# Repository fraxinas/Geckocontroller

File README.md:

# Geckocontroller

(CC) 2021-2022 by Andreas Frisch <github@fraxinas.dev>

## OwO what's this?
**`geckocontroller` is an ESP32-based all-in-one solution for terrarium automation.**

|  |  |
| :------------------------------------------ | :----------------------------------------- |

## Hardware Features
### Relay Output
* 3 solid state relays with zero-cross switching
* individual load 1A each
* for HeatBed (/Fogger), HeatLamp and Pump

### Dimmer Output
* opto-coupler zero cross detection
* random cross solid state relay
* phase controller modulator

### RGB LED Output
* PWM driver
* for 12V RGB LED stripes

### FAN Output
* for an ATX type PC fan
* PWM and tachometer pins
* power cut-off circuitry for completely stopping all types of fans

### Dallas Thermometer Input
* 2 inputs for DS18B20 bus temperature sensors

### I²C Ports
* BME280 Thermo/Hygro/Baro sensor module (ceiling)
* SHT-3xD Thermo/Hygro sensor (ground)

### Load Cell Input
* HX711-based load cell amplifier/ADC
* for weighing / occupancy detection

### USB-C Port
* USB-to-serial programming port

### WiFi
* ESP32 wifi client

### SPI / Addon Connector
* for future extensions like a display or console

### Documentation
* [Circuit Calculations](hardware/calculations/README.md)

## Software

### Using ESPHome.io
* simple YAML configuration for different sensor / actor modules
* Through Home Assistant web interface:
  * data logging and visualization of all environmental readings
  * manually control all actors, modify set points of controllers

### Weather Simulation
* use Nouvelle-Calédonie (Crested Gecko's natural habitat) real weather records
* use temperature, humidity, rain and sky cover values for creating a realistic varied simulation of the habitants' indigenous environment
* simulated sunrise, sunset, lightening storm

### Documentation
* [How-to Setup & Calibrate](software/README.md)

## Console unit
|     |     |
| :------------------------------------------ | :----------------------------------------- |
* Stand-alone device based on ESP32
* remote controls the main unit through home assistant via WiFi
* 240x240 IPS Display
* Rotary encoder + navigation button
* MH-Z19 CO<sub>2</sub> Sensor
* 6x WS2812 addressable RGB LEDs
* Piezo Buzzer for audio alerts
* USB-C powered
* custom esphome components:
  * controls for thermostat, hygrostat, rain, fogger
  * HSV color picker for scenic light

## TODO
### Console unit
- [X] schematic & PCB layout
- [ ] 3d case
- [X] CO2 sensor
- [X] WS2812 RGB LEDs
- [X] buzzer
- [X] software for ST7789 display
- [X] software for rotary encoder
- [ ] VCNL4040 support
- [ ] photos / documentation

### Controller unit
- [x] 3d-printed cases for BME280 sensor and console
- [x] rainfall/humidity automation
- [x] ventilation automation
- [x] moonlight simulation
- [x] thunderstorm simulation
- [ ] photos / documentation

## Project Diary
| Date       | Version | Milestone                                        |
| :--------- | :------ | :----------------------------------------------- |
| 2021-02-21 | v1.0    | Commission of 1st prototype PCB with aisler.net  |
| 2021-03-12 | v1.1    | First time programming of bodged prototype PCB   |
| 2021-04-10 |         | Fixed hardware issues with [LeoDJ](https://github.com/LeoDJ) & [Patagona](https://github.com/patagonaa) |
| 2021-04-15 | v1.2    | Commission of 2nd revision PCB with aisler.net   |
| 2021-05-03 | v1.2    | Completed PCB assembly, all modules working      |
| 2021-05-16 | v1.2    | Assembling of case and first deployment of unit  |
| 2022-01-02 |         | Added fogger to terrarium                        |
| 2022-01-09 |         | Base weather simulation on real historic records |
| 2022-01-28 | v1.0    | Order Console PCB at aisler.net & parts at LCSC  |
| 2022-02-18 |         | Assembled Console PCB                            |
| 2022-03-07 | v2.0    | New Hardware Revision of Console PCB             |

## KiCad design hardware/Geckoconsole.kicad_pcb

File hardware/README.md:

# Geckocontroller Hardware

## Calculations

### ACT4088 Feedback Resistors

with
* V<sub>out</sub> = 3.3V
* R<sub>FB1</sub> chosen 47k

* R<sub>FB2</sub> = R<sub>FB1</sub> / ((V<sub>out</sub> / 0.81) - 1) = 15289.156626506

Values are:
* `R103` = 47k
* `R101` = 15k
* `R102` = 287R

### HX711 Reference Voltage Resistors

with
* AVDD should be 100mV below VCC, so 3.20V
* AVDD = V<sub>BG</sub> * ( R1 + R2 ) / R2
* R1 chosen 47k

Values are:
* `R61` = 47k
* `R62` = 30k1

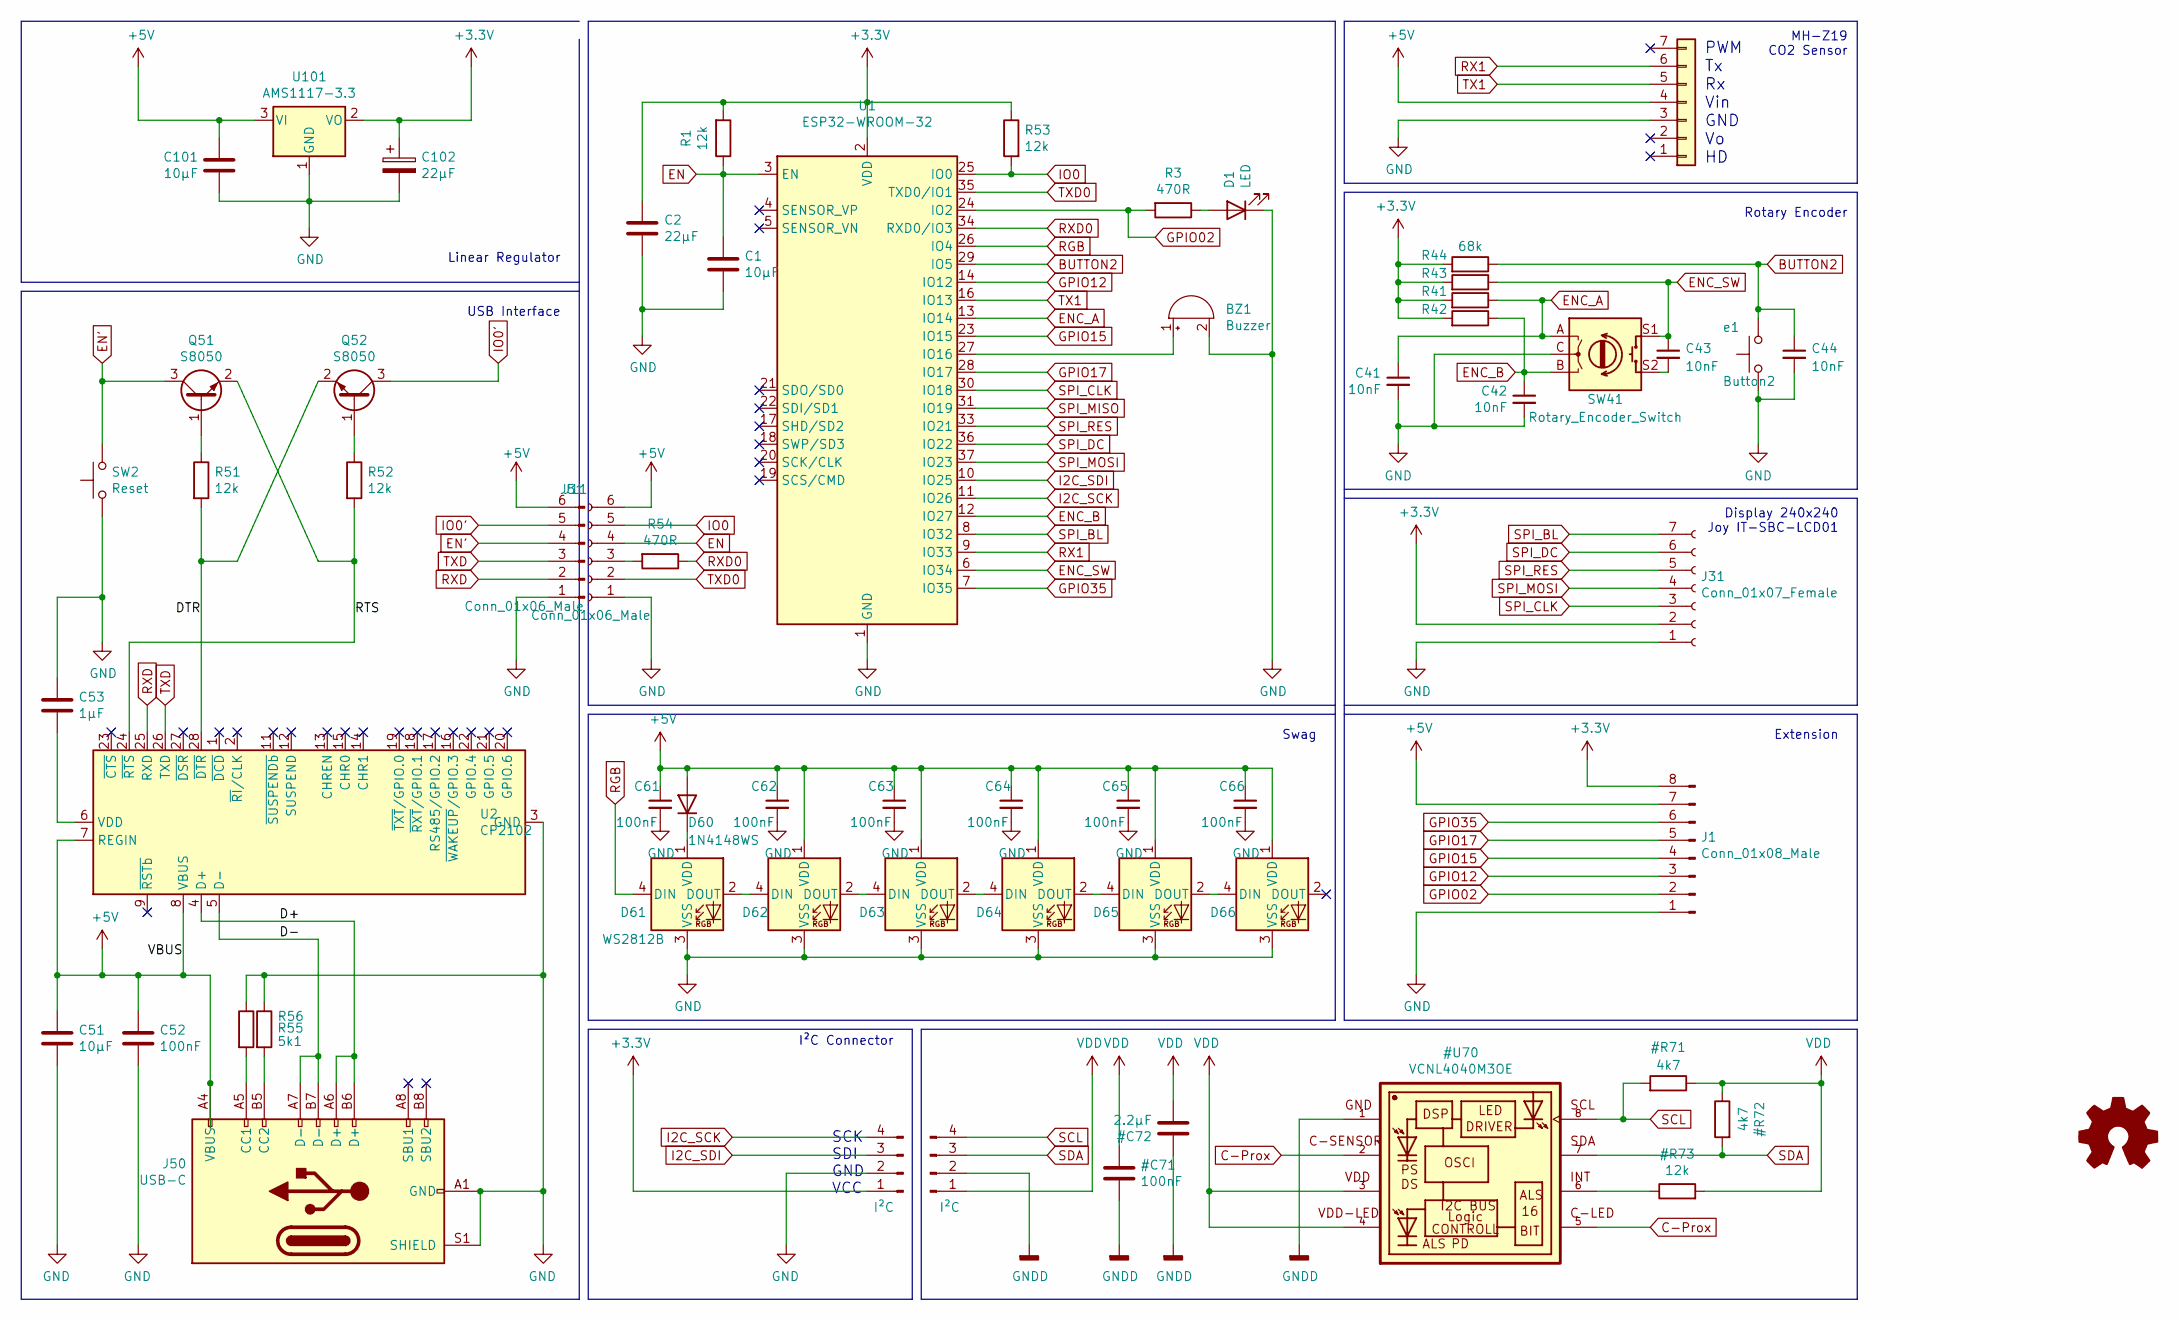
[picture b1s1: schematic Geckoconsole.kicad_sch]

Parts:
BZ1: Buzzer; Buzzer_Murata_PKMCS0909E4000-R1
C1, C51, C101: 10µF; C_0805_2012Metric_Pad1.18x1.45mm_HandSolder
C2: 22µF; C_1210_3225Metric_Pad1.33x2.70mm_HandSolder
C41, C42, C43, C44: 10nF; C_0603_1608Metric_Pad1.08x0.95mm_HandSolder
C52, C61, C62, C63, C64, C65, C66: 100nF; C_0603_1608Metric_Pad1.08x0.95mm_HandSolder
C53: 1µF; C_0603_1608Metric_Pad1.08x0.95mm_HandSolder
C102: 22µF; CP_Elec_4x5.3
D1: LED; LED_0805_2012Metric_Pad1.15x1.40mm_HandSolder
D60: 1N4148WS; D_SOD-323_HandSoldering
D61, D62, D63, D64, D65, D66: WS2812B; LED_WS2812B_PLCC4_5.0x5.0mm_P3.2mm
J1: Conn_01x08_Male; PinHeader_2x04_P2.54mm_Vertical
J11: Conn_01x06_Male; PinSocket_1x06_P2.00mm_Horizontal
J31: Conn_01x07_Female; PinSocket_1x07_P2.54mm_Vertical
J50: USB-C; USB_C_Receptacle_XKB_U262-16XN-4BVC11
J51: Conn_01x06_Male; PinHeader_1x06_P2.00mm_Horizontal
J70: I²C; PinSocket_1x04_P2.54mm_Vertical
J81: Conn_01x07; JST_PH_B7B-PH-K_1x07_P2.00mm_Vertical
LOGO1: Logo_Open_Hardware_Small; OSHW-Logo_5.7x6mm_Mask
Q51, Q52: S8050; SOT-23
R1, R51, R52, R53: 12k; R_0805_2012Metric_Pad1.20x1.40mm_HandSolder
R3, R54: 470R; R_0805_2012Metric_Pad1.20x1.40mm_HandSolder
R41, R42, R43, R44: 68k; R_0805_2012Metric_Pad1.20x1.40mm_HandSolder
R55, R56: 5k1; R_0805_2012Metric_Pad1.20x1.40mm_HandSolder
SW2: Reset; SW_SPST_B3U-1000P-B
SW41: Rotary_Encoder_Switch; Rotary_Encoder_Switched_PEC11R
U1: ESP32-WROOM-32
U2: CP2102; CP2102-QFN-28-modified
U101: AMS1117-3.3; SOT-223-3_TabPin2
e1: Button2; SW_PUSH_6mm_H5mm

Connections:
+3V3: C2.1, C102.1, J1.8, J31.2, J70.1, R1.2, R41.2, R42.2, R43.2, R44.2, R53.1, U1.2 (VDD), U101.2 (VO)
+5V: C51.1, C52.1, C61.1, C62.1, C63.1, C64.1, C65.1, C66.1, C101.1, D60.2 (A), D62.1 (VDD), D63.1 (VDD), D64.1 (VDD), D65.1 (VDD), D66.1 (VDD), J1.7, J11.6, J50.A4 (VBUS), J50.A9 (VBUS), J50.B4 (VBUS), J50.B9 (VBUS), J51.6, J81.4, U2.7 (REGIN), U2.8 (VBUS), U101.3 (VI)
/D+: J50.A6 (D+), J50.B6 (D+), U2.4 (D+)
/D-: J50.A7 (D-), J50.B7 (D-), U2.5 (D-)
/DTR: Q52.2 (E), R51.2, U2.28 (~DTR)
/RTS: Q51.2 (E), R52.2, U2.24 (~RTS)
BUTTON2: C44.1, R44.1, U1.29 (IO5), e1.2
EN: C1.1, J11.4, R1.1, U1.3 (EN)
EN': J51.4, Q51.3 (C), SW2.2
ENC_A: C41.1, R41.1, SW41.A, U1.13 (IO14)
ENC_B: C42.1, R42.1, SW41.B, U1.12 (IO27)
ENC_SW: C43.1, R43.1, SW41.S1, U1.6 (IO34)
GND: BZ1.2 (+), C1.2, C2.2, C41.2, C42.2, C44.2, C51.2, C52.2, C53.1, C61.2, C62.2, C63.2, C64.2, C65.2, C66.2, C101.2, C102.2, D1.1 (K), D61.3 (VSS), D62.3 (VSS), D63.3 (VSS), D64.3 (VSS), D65.3 (VSS), D66.3 (VSS), J1.1, J11.1, J31.1, J50.A1 (GND), J50.A12 (GND), J50.B1 (GND), J50.B12 (GND), J50.S1 (SHIELD), J51.1, J70.2, J81.3, R55.1, R56.1, SW2.1, SW41.C, U1.1 (GND), U1.15 (GND), U1.38 (GND), U1.39 (GND), U2.3 (GND), U2.29 (GND), U101.1 (GND), e1.1
GPIO02: J1.2, R3.2, U1.24 (IO2)
GPIO12: J1.3, U1.14 (IO12)
GPIO15: J1.4, U1.23 (IO15)
GPIO17: J1.5, U1.28 (IO17)
GPIO35: J1.6, U1.7 (IO35)
I2C_SCK: J70.4, U1.11 (IO26)
I2C_SDI: J70.3, U1.10 (IO25)
IO0: J11.5, R53.2, U1.25 (IO0)
IO0': J51.5, Q52.3 (C)
unnamed: BZ1.1 (-), U1.27 (IO16)
unnamed: C43.2, SW41.S2
unnamed: C53.2, U2.6 (VDD)
unnamed: D1.2 (A), R3.1
unnamed: D60.1 (K), D61.1 (VDD)
unnamed: D61.2 (DOUT), D62.4 (DIN)
unnamed: D62.2 (DOUT), D63.4 (DIN)
unnamed: D63.2 (DOUT), D64.4 (DIN)
unnamed: D64.2 (DOUT), D65.4 (DIN)
unnamed: D65.2 (DOUT), D66.4 (DIN)
unnamed: J11.3, R54.2
unnamed: J50.A5 (CC1), R56.2
unnamed: J50.B5 (CC2), R55.2
unnamed: Q51.1 (B), R51.1
unnamed: Q52.1 (B), R52.1
RGB: D61.4 (DIN), U1.26 (IO4)
RX1: J81.6, U1.9 (IO33)
RXD: J51.2, U2.25 (RXD)
RXD0: R54.1, U1.34 (RXD0/IO3)
SPI_BL: J31.7, U1.8 (IO32)
SPI_CLK: J31.3, U1.30 (IO18)
SPI_DC: J31.6, U1.36 (IO22)
SPI_MISO: U1.31 (IO19)
SPI_MOSI: J31.4, U1.37 (IO23)
SPI_RES: J31.5, U1.33 (IO21)
TX1: J81.5, U1.16 (IO13)
TXD: J51.3, U2.26 (TXD)
TXD0: J11.2, U1.35 (TXD0/IO1)

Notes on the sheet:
Display 240x240 Joy IT-SBC-LCD01
USB Interface
SCK SDI GND VCC
Linear Regulator
PWM Tx Rx Vin GND Vo HD
Rotary Encoder
I²C Connector
Swag
MH-Z19 CO2 Sensor
Extension

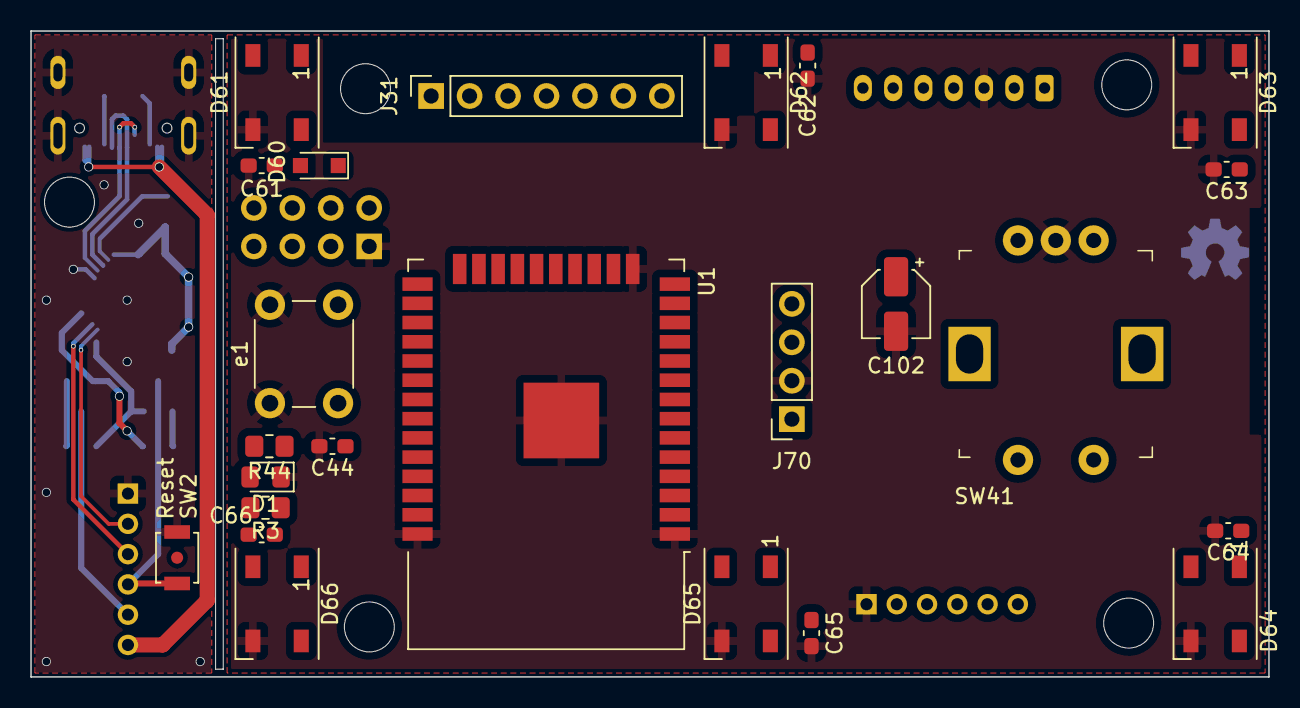
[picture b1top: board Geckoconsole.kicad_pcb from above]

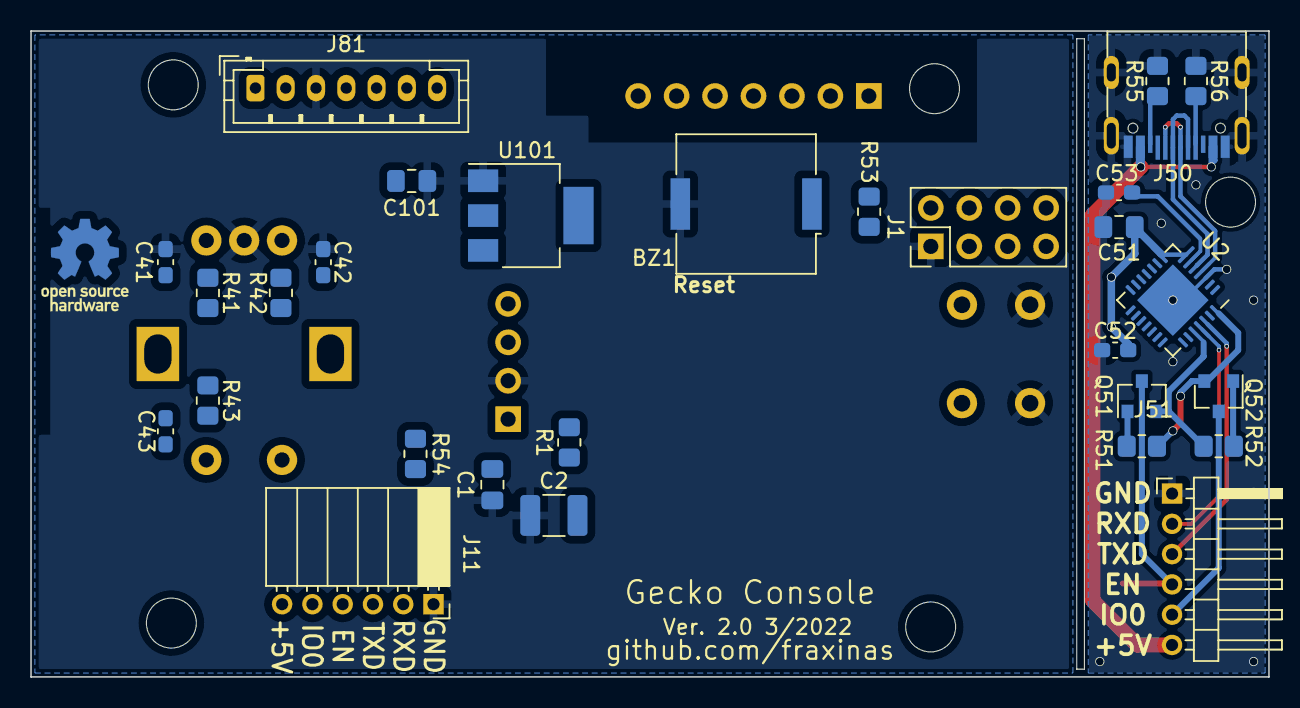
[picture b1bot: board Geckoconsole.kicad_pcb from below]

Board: 2 copper layers, 81.8 x 42.7 mm, 54 parts (30 on the bottom side), 49 nets.

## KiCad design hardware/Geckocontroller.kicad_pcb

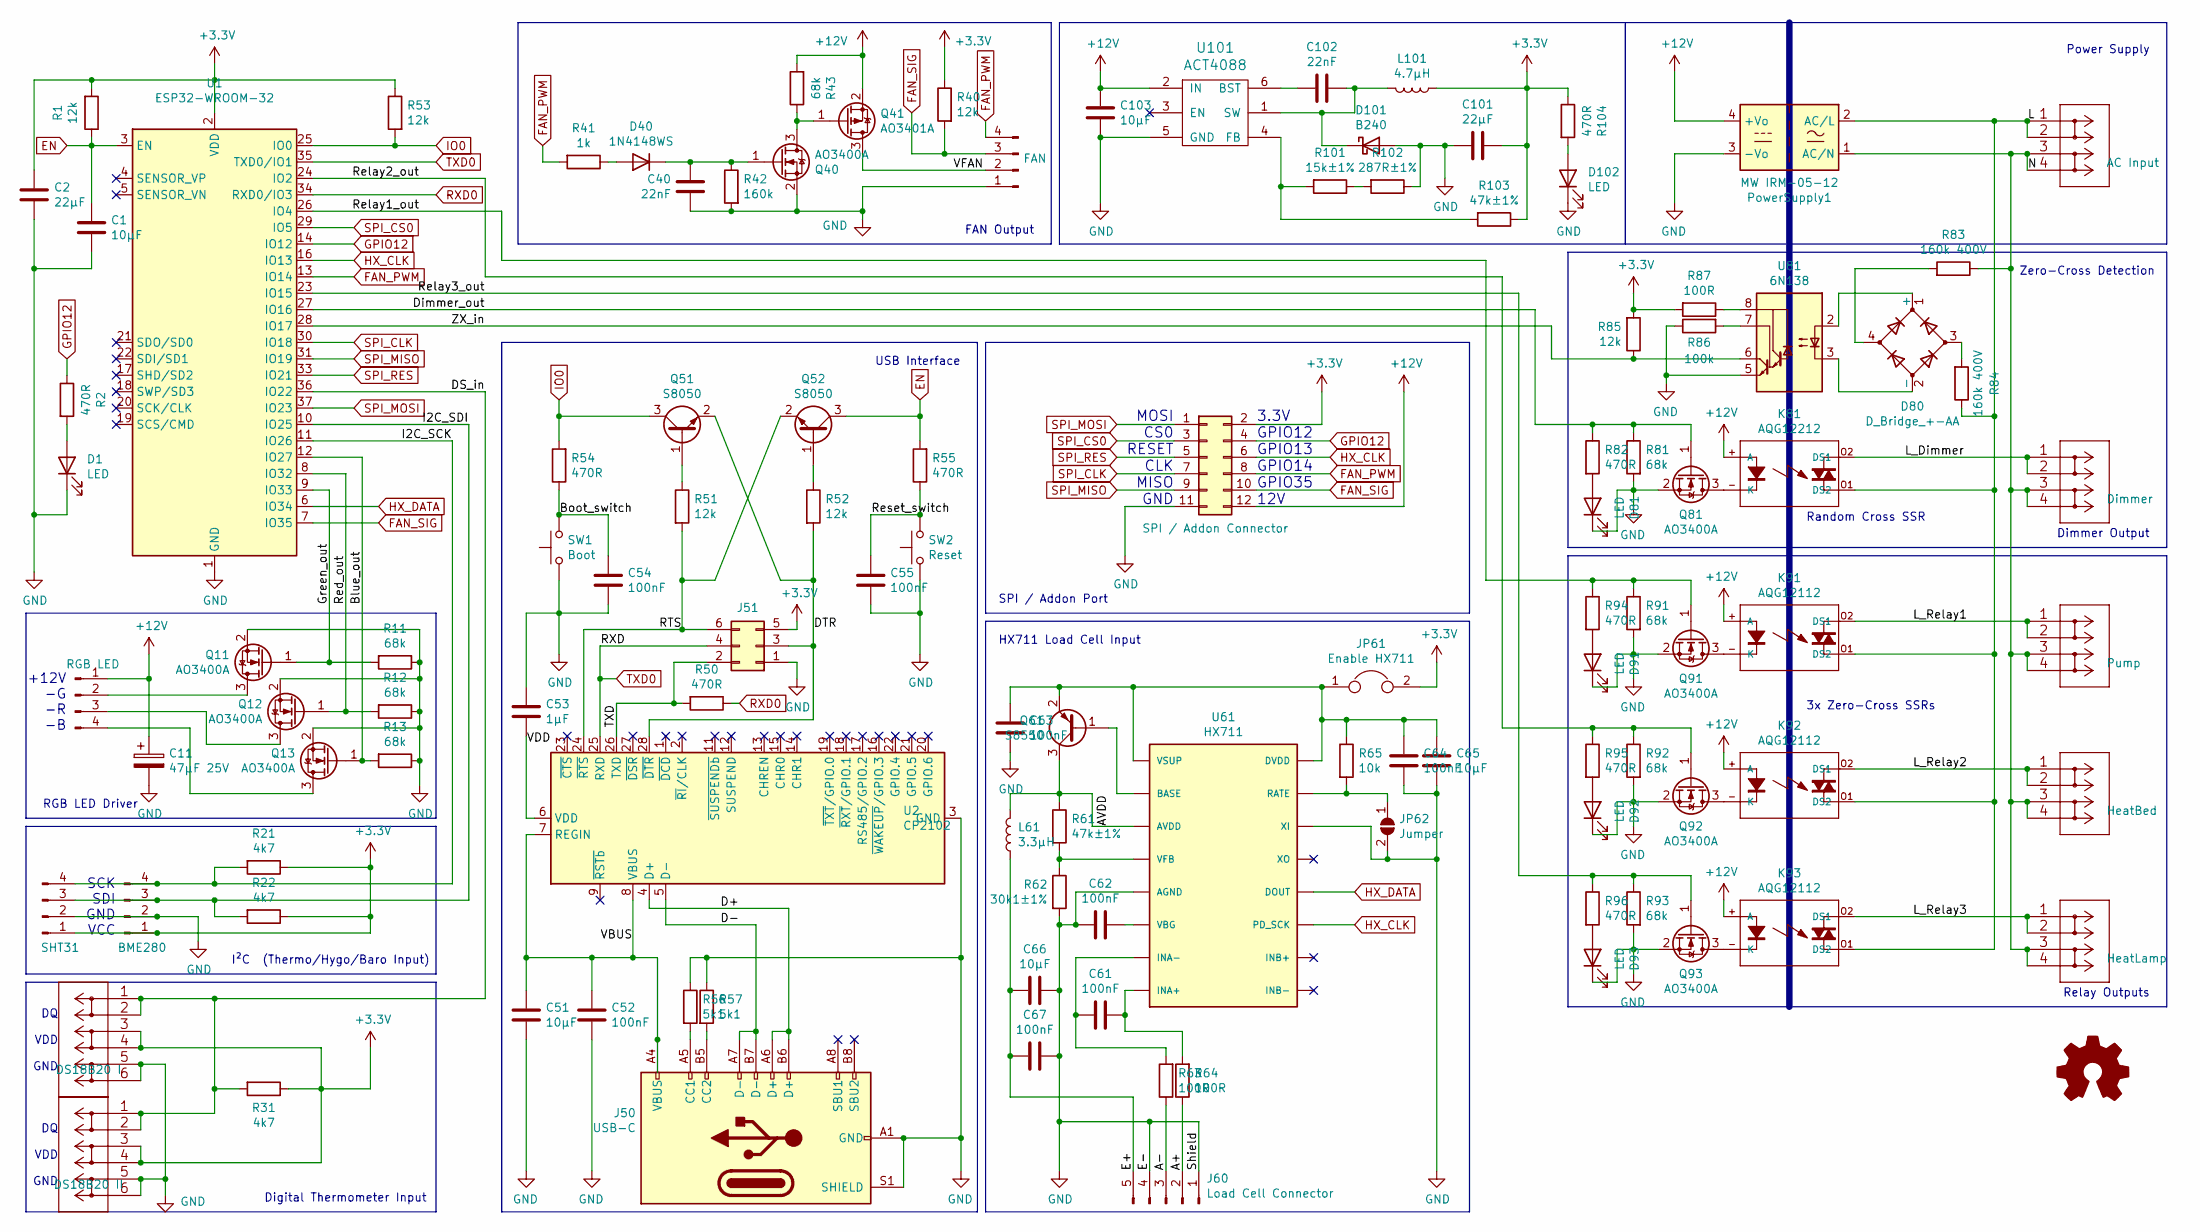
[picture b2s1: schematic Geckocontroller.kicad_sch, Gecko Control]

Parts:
C1, C51, C65, C66, C103: 10µF; C_0805_2012Metric_Pad1.18x1.45mm_HandSolder
C2, C101: 22µF; C_1210_3225Metric_Pad1.33x2.70mm_HandSolder
C11: 47µF 25V; CP_Radial_D5.0mm_P2.50mm
C40, C102: 22nF; C_0603_1608Metric_Pad1.08x0.95mm_HandSolder
C52, C54, C55, C61, C62, C63, C64, C67: 100nF; C_0603_1608Metric_Pad1.08x0.95mm_HandSolder
C53: 1µF; C_0805_2012Metric_Pad1.18x1.45mm_HandSolder
D1, D81, D91, D92, D93, D102: LED; LED_0805_2012Metric_Pad1.15x1.40mm_HandSolder
D40: 1N4148WS; D_SOD-323_HandSoldering
D80: D_Bridge_+-AA; TO-269AA
D101: B240; D_SMB
J1: SHT31; JST_PH_B4B-PH-K_1x04_P2.00mm_Vertical
J11: RGB LED; JST_XH_B4B-XH-A_1x04_P2.50mm_Vertical
J21: BME280; JST_PH_B4B-PH-K_1x04_P2.00mm_Vertical
J31: DS18B20 I; WAGO-2604-1103-bare
J32: DS18B20 II; WAGO-2604-1103-bare
J40: FAN; Molex_KK-254_AE-6410-04A_1x04_P2.54mm_Vertical
J50: USB-C; USB_C_Receptacle_XKB_U262-16XN-4BVC11
J51: UART; PinSocket_2x03_P2.54mm_Vertical
J60: Load Cell Connector; JST_PH_B5B-PH-K_1x05_P2.00mm_Vertical
J70: SPI / Addon Connector; IDC-Header_2x06_P2.54mm_Vertical
J81: Dimmer; WAGO-2604-1102
J91: Pump; WAGO-2604-1102
J92: HeatBed; WAGO-2604-1102-bare
J93: HeatLamp; WAGO-2604-1102-bare
J101: AC Input; WAGO-2604-1102
JP61: Enable HX711; PinHeader_1x02_P2.54mm_Vertical
JP62: Jumper; SolderJumper-2_Open_Mini
K81: AQG12212; AQG22224
K91, K92, K93: AQG12112; AQG22224
L61: 3.3µH; L_1008_2520Metric_Pad1.43x2.20mm_HandSolder
L101: 4.7µH; L_1008_2520Metric_Pad1.43x2.20mm_HandSolder
LOGO1: Logo_Open_Hardware_Small; OSHW-Logo2_14.6x12mm_Mask
PowerSupply1: MW IRM-05-12; Converter_ACDC_MeanWell_IRM-05-xx_THT
Q11, Q12, Q13, Q40, Q81, Q91, Q92, Q93: AO3400A; SOT-23
Q41: AO3401A; SOT-23
Q51, Q52: S8050; SOT-23
Q61: S8550; SOT-23
R1, R40, R51, R52, R53, R85: 12k; R_0805_2012Metric_Pad1.20x1.40mm_HandSolder
R2, R50, R54, R55, R82, R94, R95, R96, R104: 470R; R_0805_2012Metric_Pad1.20x1.40mm_HandSolder
R11, R12, R13, R43, R81, R91, R92, R93: 68k; R_0805_2012Metric_Pad1.20x1.40mm_HandSolder
R21, R22, R31: 4k7; R_0805_2012Metric_Pad1.20x1.40mm_HandSolder
R41: 1k; R_0805_2012Metric_Pad1.20x1.40mm_HandSolder
R42: 160k; R_0805_2012Metric_Pad1.20x1.40mm_HandSolder
R56, R57: 5k1; R_0805_2012Metric_Pad1.20x1.40mm_HandSolder
R61, R103: 47k±1%; R_0805_2012Metric_Pad1.20x1.40mm_HandSolder
R62: 30k1±1%; R_0805_2012Metric_Pad1.20x1.40mm_HandSolder
R63, R64, R87: 100R; R_0603_1608Metric_Pad0.98x0.95mm_HandSolder
R65: 10k; R_0805_2012Metric_Pad1.20x1.40mm_HandSolder
R83, R84: 160k 400V; R_1206_3216Metric_Pad1.30x1.75mm_HandSolder
R86: 100k; R_0805_2012Metric_Pad1.20x1.40mm_HandSolder
R101: 15k±1%; R_0805_2012Metric_Pad1.20x1.40mm_HandSolder
R102: 287R±1%; R_0805_2012Metric_Pad1.20x1.40mm_HandSolder
SW1: Boot; SW_PUSH_6mm
SW2: Reset; SW_PUSH_6mm
U1: ESP32-WROOM-32
U2: CP2102; CP2102-QFN-28-modified
U61: HX711; SO16
U81: 6N138; SMDIP-8_W9.53mm
U101: ACT4088; SOT-23-6_Handsoldering

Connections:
+3V3: C2.1, C101.1, J1.1, J21.1, J31.3, J31.4, J32.3, J32.4, J51.5, J70.2, JP61.2, L101.1, R1.2, R21.1, R22.1, R31.1, R40.1, R53.1, R85.2, R87.2, R103.1, R104.1, U1.2 (VDD)
+12V: C11.1, C103.1, J11.1, J70.12, K81.+ (A), K91.+ (A), K92.+ (A), K93.+ (A), PowerSupply1.4 (+Vo), Q41.2 (S), R43.2, U101.2 (IN)
/A+: J60.2, R64.1
/A-: J60.3, R63.1
/AVDD: L61.2, Q61.3 (C), R61.1, U61.3 (AVDD)
/Blue_out: Q13.1 (G), R13.2, U1.12 (IO27)
/Boot_switch: C54.1, R54.1, SW1.2
/D+: J50.A6 (D+), J50.B6 (D+), U2.4 (D+)
/D-: J50.A7 (D-), J50.B7 (D-), U2.5 (D-)
/DS_in: J31.1, J31.2, J32.1, J32.2, R31.2, U1.36 (IO22)
/DTR: J51.3, Q51.2 (E), R52.2, U2.28 (~DTR)
/Dimmer_out: Q81.1 (G), R81.1, R82.1, U1.27 (IO16)
/E+: C66.2, C67.2, J60.5, L61.1
/Green_out: Q11.1 (G), R11.2, U1.9 (IO33)
/I2C_SCK: J1.4, J21.4, R21.2, U1.11 (IO26)
/I2C_SDI: J1.3, J21.3, R22.2, U1.10 (IO25)
/L: J101.1, J101.2, K81.O1 (DS2), K91.O1 (DS2), K92.O1 (DS2), K93.O1 (DS2), PowerSupply1.2 (AC/L), R84.1
/L_Dimmer: J81.1, J81.2, K81.O2 (DS1)
/L_Relay1: J91.1, J91.2, K91.O2 (DS1)
/L_Relay2: J92.1, J92.2, K92.O2 (DS1)
/L_Relay3: J93.1, J93.2, K93.O2 (DS1)
/N: J81.3, J81.4, J91.3, J91.4, J92.3, J92.4, J93.3, J93.4, J101.3, J101.4, PowerSupply1.1 (AC/N), R83.1
/RTS: J51.6, Q52.2 (E), R51.2, U2.24 (~RTS)
/Red_out: Q12.1 (G), R12.2, U1.8 (IO32)
/Relay1_out: Q91.1 (G), R91.1, R94.1, U1.26 (IO4)
/Relay2_out: Q92.1 (G), R92.1, R95.1, U1.24 (IO2)
/Relay3_out: Q93.1 (G), R93.1, R96.1, U1.23 (IO15)
/Reset_switch: C55.1, R55.1, SW2.2
/TXD: J51.2, R50.2, U2.26 (TXD)
/VBUS: C51.1, C52.1, J50.A4 (VBUS), J50.A9 (VBUS), J50.B4 (VBUS), J50.B9 (VBUS), U2.7 (REGIN), U2.8 (VBUS)
/VDD: C53.2, U2.6 (VDD)
/VFAN: J40.2, Q41.3 (D)
/ZX_in: R85.1, U1.28 (IO17), U81.6 (VO2)
EN: C1.1, Q52.3 (C), R1.1, R55.2, U1.3 (EN)
FAN_PWM: J40.4, J70.8, R41.2, U1.13 (IO14)
FAN_SIG: J40.3, J70.10, R40.2, U1.7 (IO35)
GND: C1.2, C2.2, C11.2, C40.1, C51.2, C52.2, C53.1, C54.2, C55.2, C62.2, C63.2, C64.2, C65.2, C66.1, C67.1, C101.2, C103.2, D1.1 (K), D81.1 (K), D91.1 (K), D92.1 (K), D93.1 (K), D101.2 (A), D102.1 (K), J1.2, J21.2, J31.5, J31.6, J32.5, J32.6, J40.1, J50.A1 (GND), J50.A12 (GND), J50.B1 (GND), J50.B12 (GND), J50.S1 (SHIELD), J51.1, J60.1, J60.4, J70.11, JP62.2 (B), PowerSupply1.3 (-Vo), Q11.2 (S), Q12.2 (S), Q13.2 (S), Q40.2 (S), Q81.2 (S), Q91.2 (S), Q92.2 (S), Q93.2 (S), R11.1, R12.1, R13.1, R42.2, R56.1, R57.1, R62.2, R81.2, R86.1, R91.2, R92.2, R93.2, R102.1, SW1.1, SW2.1, U1.1 (GND), U1.15 (GND), U1.38 (GND), U1.39 (GND), U2.3 (GND), U2.29 (GND), U61.5 (AGND), U61.14 (XI), U81.5 (GND), U101.5 (GND)
GPIO12: J70.4, R2.1, U1.14 (IO12)
HX_CLK: J70.6, U1.16 (IO13), U61.11 (PD_SCK)
HX_DATA: U1.6 (IO34), U61.12 (DOUT)
IO0: Q51.3 (C), R53.2, R54.2, U1.25 (IO0)
unnamed: C40.2, D40.1 (K), Q40.1 (G), R42.1
unnamed: C61.1, R63.2, U61.7 (INA-)
unnamed: C61.2, R64.2, U61.8 (INA+)
unnamed: C62.1, U61.6 (VBG)
unnamed: C63.1, C64.1, C65.1, JP61.1, Q61.2 (E), R65.1, U61.1 (VSUP), U61.16 (DVDD)
unnamed: C102.1, D101.1 (K), L101.2, U101.1 (SW)
unnamed: C102.2, U101.6 (BST)
unnamed: D1.2 (A), R2.2
unnamed: D40.2 (A), R41.1
unnamed: D80.1 (+), U81.2 (C1)
unnamed: D80.2 (-), U81.3 (C2)
unnamed: D80.3, R84.2
unnamed: D80.4, R83.2
unnamed: D81.2 (A), R82.2
unnamed: D91.2 (A), R94.2
unnamed: D92.2 (A), R95.2
unnamed: D93.2 (A), R96.2
unnamed: D102.2 (A), R104.2
unnamed: J11.2, Q11.3 (D)
unnamed: J11.3, Q12.3 (D)
unnamed: J11.4, Q13.3 (D)
unnamed: J50.A5 (CC1), R56.2
unnamed: J50.B5 (CC2), R57.2
unnamed: JP62.1 (A), R65.2, U61.15 (RATE)
unnamed: K81.- (K), Q81.3 (D)
unnamed: K91.- (K), Q91.3 (D)
unnamed: K92.- (K), Q92.3 (D)
unnamed: K93.- (K), Q93.3 (D)
unnamed: Q40.3 (D), Q41.1 (G), R43.1
unnamed: Q51.1 (B), R51.1
unnamed: Q52.1 (B), R52.1
unnamed: Q61.1 (B), U61.2 (BASE)
unnamed: R61.2, R62.1, U61.4 (VFB)
unnamed: R86.2, U81.7 (VO1)
unnamed: R87.1, U81.8 (VCC)
unnamed: R101.1, R102.2
unnamed: R101.2, R103.2, U101.4 (FB)
RXD0: R50.1, U1.34 (RXD0/IO3)
SPI_CLK: J70.7, U1.30 (IO18)
SPI_CS0: J70.3, U1.29 (IO5)
SPI_MISO: J70.9, U1.31 (IO19)
SPI_MOSI: J70.1, U1.37 (IO23)
SPI_RES: J70.5, U1.33 (IO21)
TXD0: J51.4, U1.35 (TXD0/IO1), U2.25 (RXD)

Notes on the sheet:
Relay Outputs
SCK SDI GND VCC
FAN Output
HX711 Load Cell Input
I²C (Thermo/Hygo/Baro Input)
MOSI CS0 RESET CLK MISO GND
DQ VDD GND
SPI / Addon Port
RGB LED Driver
3.3V GPIO12 GPIO13 GPIO14 GPIO35 12V
3x Zero-Cross SSRs
Digital Thermometer Input
Power Supply
Dimmer Output
Zero-Cross Detection
+12V -G -R -B
USB Interface
Random Cross SSR

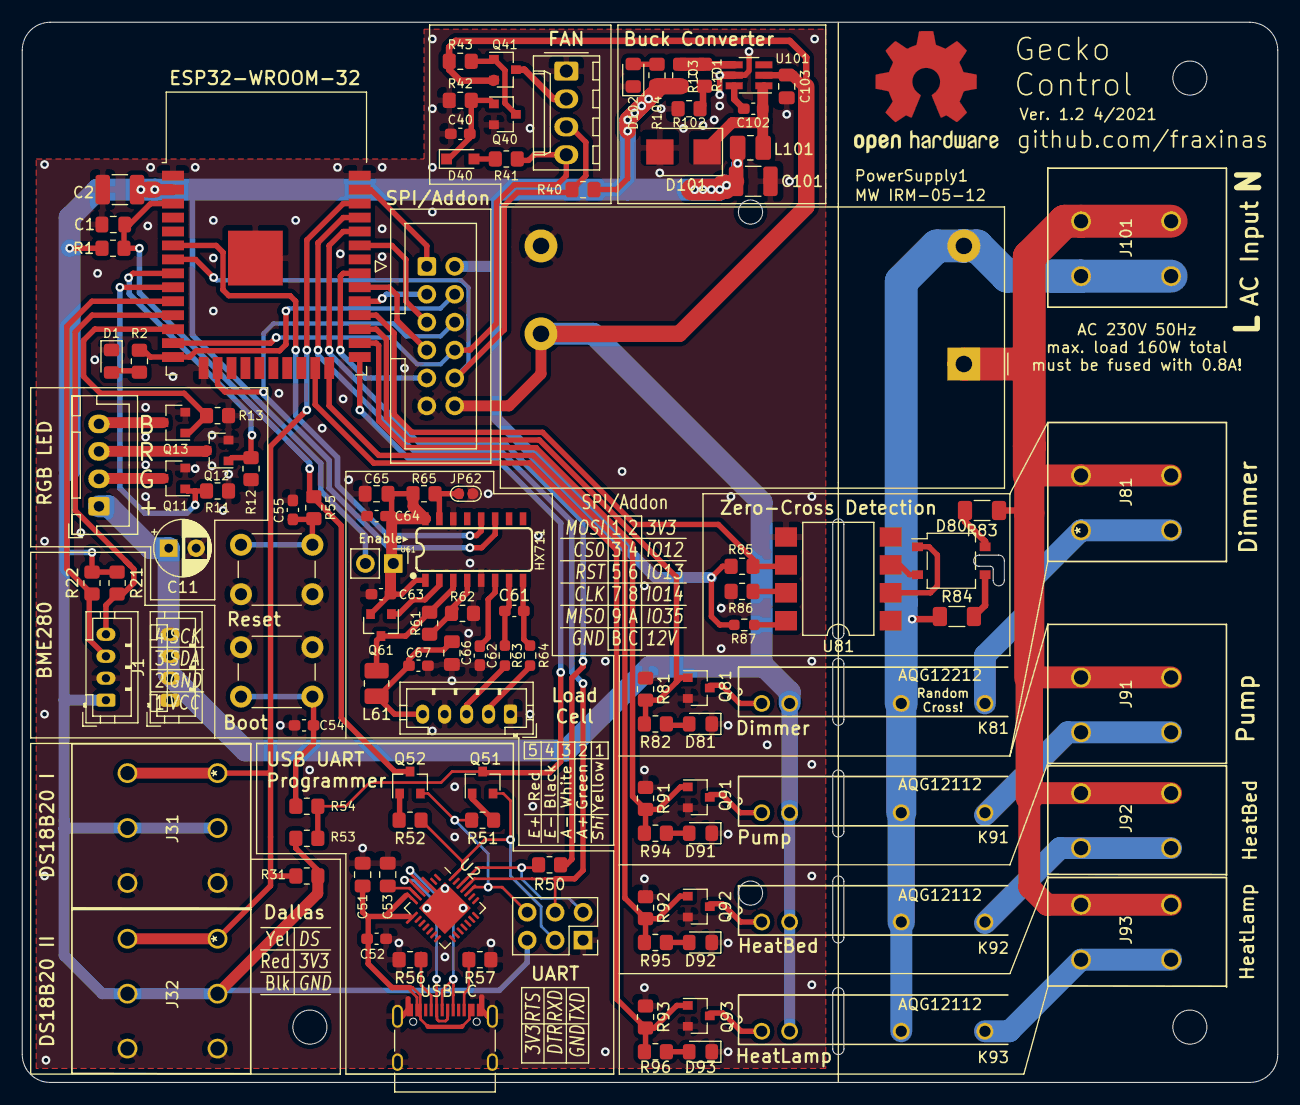
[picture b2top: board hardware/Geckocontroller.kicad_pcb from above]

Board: 2 copper layers, 114.3 x 96.5 mm, 114 parts (0 on the bottom side), 85 nets.

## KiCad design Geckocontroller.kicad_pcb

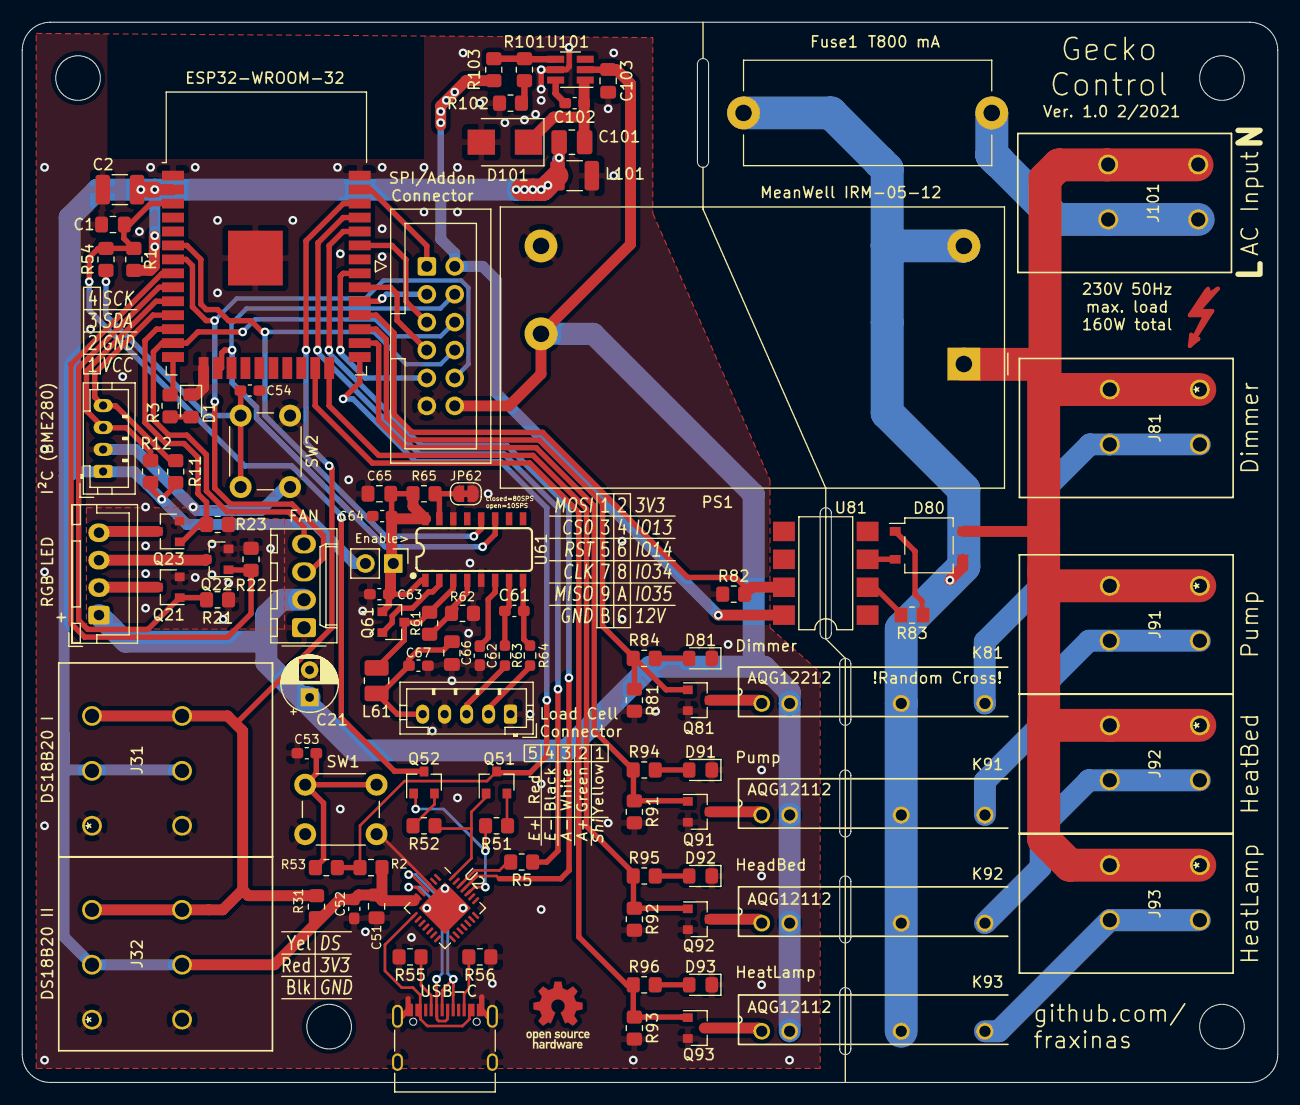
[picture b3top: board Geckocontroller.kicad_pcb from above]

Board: 2 copper layers, 114.3 x 96.5 mm, 98 parts (0 on the bottom side), 77 nets.

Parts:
C1, C51, C65, C66, C103: 10µF; C_0805_2012Metric_Pad1.18x1.45mm_HandSolder
C2, C101: 22µF; C_1210_3225Metric_Pad1.33x2.70mm_HandSolder
C21: 47µF 25V; CP_Radial_D5.0mm_P2.50mm
C52, C53, C54, C61, C62, C63, C64, C67: 100nF; C_0603_1608Metric_Pad1.08x0.95mm_HandSolder
C102: 22nF; C_0603_1608Metric_Pad1.08x0.95mm_HandSolder
D1, D81, D91, D92, D93: LED; LED_0805_2012Metric_Pad1.15x1.40mm_HandSolder
D80: D_Bridge_+-AA; TO-269AA
D101: B240; D_SMB
Fuse1: T800 mA; Fuseholder_Cylinder-5x20mm_Stelvio-Kontek_PTF78_Horizontal_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
J11: I²C (BME280); JST_PH_B4B-PH-K_1x04_P2.00mm_Vertical
J21: RGB LED; JST_XH_B4B-XH-A_1x04_P2.50mm_Vertical
J31: DS18B20 I; 2604-1103
J32: DS18B20 II; 2604-1103
J40: FAN; Molex_KK-254_AE-6410-04A_1x04_P2.54mm_Vertical
J51: USB-C; USB_C_Receptacle_XKB_U262-16XN-4BVC11
J60: Load Cell Connector; JST_PH_B5B-PH-K_1x05_P2.00mm_Vertical
J70: SPI / Addon Connector; IDC-Header_2x06_P2.54mm_Vertical
J81: Dimmer; 2604-1102
J91: Pump; 2604-1102
J92: HeatBed; 2604-1102
J93: HeatLamp; 2604-1102
J101: AC Input; 2604-1102
JP61: Enable>; PinHeader_1x02_P2.54mm_Vertical
JP62: Jumper; SolderJumper-2_P1.3mm_Bridged_RoundedPad1.0x1.5mm
K81: AQG12212; AQG22224
K91, K92, K93: AQG12112; AQG22224
L61: 3.3µH; L_1008_2520Metric_Pad1.43x2.20mm_HandSolder
L101: 4.7µH; L_1008_2520Metric_Pad1.43x2.20mm_HandSolder
PS1: MeanWell IRM-05-12; Converter_ACDC_MeanWell_IRM-05-xx_THT
Q21, Q22, Q23, Q81, Q91, Q92, Q93: AO3400A; SOT-23
Q51, Q52: S8050; SOT-23
Q61: S8550; SOT-23
R1, R2, R51, R52: 12k; R_0805_2012Metric_Pad1.20x1.40mm_HandSolder
R3, R5, R53, R54, R84, R94, R95, R96: 470R; R_0805_2012Metric_Pad1.20x1.40mm_HandSolder
R11, R12, R31: 4k7; R_0805_2012Metric_Pad1.20x1.40mm_HandSolder
R21, R22, R23, R81, R91, R92, R93: 68k; R_0805_2012Metric_Pad1.20x1.40mm_HandSolder
R55, R56: 5k1; R_0805_2012Metric_Pad1.20x1.40mm_HandSolder
R61, R103: 47k±1%; R_0805_2012Metric_Pad1.20x1.40mm_HandSolder
R62: 30k1±1%; R_0805_2012Metric_Pad1.20x1.40mm_HandSolder
R63, R64: 100R; R_0603_1608Metric_Pad0.98x0.95mm_HandSolder
R65, R82: 10k; R_0805_2012Metric_Pad1.20x1.40mm_HandSolder
R83: 330kR; R_0805_2012Metric_Pad1.20x1.40mm_HandSolder
R101: 15k±1%; R_0805_2012Metric_Pad1.20x1.40mm_HandSolder
R102: 287R±1%; R_0805_2012Metric_Pad1.20x1.40mm_HandSolder
SW1, SW2: SW_Push; SW_PUSH_6mm
U1: ESP32-WROOM-32
U2: CP2102; QFN-28-1EP_5x5mm_P0.5mm_EP3.35x3.35mm
U61: HX711; SO16
U81: 6N138; SMDIP-8_W7.62mm
U101: ACT4088; SOT-23-6_Handsoldering

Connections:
+3V3: C2.1, C51.1, C52.1, C101.1, J11.1, J31.3, J31.4, J32.3, J32.4, J70.2, JP61.2, L101.2, R1.2, R2.1, R11.1, R12.1, R31.1, R103.1, U1.2, U2.6, U2.7, U81.8
+12V: C21.1, C103.1, J21.1, J40.2, J70.12, K81.+, K91.+, K92.+, K93.+, PS1.4, U101.2
/A+: J60.2, R64.1
/A-: J60.3, R63.1
/AVDD: L61.2, Q61.3, R61.1, U61.3
/Blue_out: Q23.1, R23.2, U1.12
/Boot_switch: C53.1, R53.1, SW1.2
/D+: J51.A6, J51.B6, U2.4
/D-: J51.A7, J51.B7, U2.5
/DS_in: J31.5, J31.6, J32.5, J32.6, R31.2, U1.36
/DTR: Q51.1, R52.2, U2.28
/Dimmer_out: Q81.1, R81.1, R84.1, U1.27
/E+: C66.2, C67.2, J60.5, L61.1
/Green_out: Q21.1, R21.2, U1.9
/I2C_SCK: J11.4, R11.2, U1.11
/I2C_SDI: J11.3, R12.2, U1.10
/L: Fuse1.1, J101.3, J101.4
/L': D80.3, Fuse1.2, K81.O1, K91.O1, K92.O1, K93.O1, PS1.2
/L_Dimmer: J81.3, J81.4, K81.O2
/L_Relay1: J91.3, J91.4, K91.O2
/L_Relay2: J92.3, J92.4, K92.O2
/L_Relay3: J93.3, J93.4, K93.O2
/N: D80.4, J81.1, J81.2, J91.1, J91.2, J92.1, J92.2, J93.1, J93.2, J101.1, J101.2, PS1.1
/RTS: Q52.1, R51.2, U2.24
/Red_out: Q22.1, R22.2, U1.8
/Relay1_out: Q91.1, R91.1, R94.1, U1.26
/Relay2_out: Q92.1, R92.1, R95.1, U1.24
/Relay3_out: Q93.1, R93.1, R96.1, U1.23
/Reset_switch: C54.1, R54.1, SW2.2
/TXD': R5.2, U1.35
/VBUS: J51.A4, J51.A9, J51.B4, J51.B9, U2.8
/ZX_in: R82.2, U1.28, U81.7
EN: C1.1, Q52.3, R1.1, R54.2, U1.3
FAN_PWM: J40.4, J70.6, U1.13
FAN_SIG: J40.3, J70.10, U1.7
GND: C1.2, C2.2, C21.2, C51.2, C52.2, C53.2, C54.2, C62.2, C63.2, C64.2, C65.2, C66.1, C67.1, C101.2, C103.2, D1.1, D81.1, D91.1, D92.1, D93.1, D101.2, J11.2, J31.1, J31.2, J32.1, J32.2, J40.1, J51.A1, J51.A12, J51.B1, J51.B12, J51.S1, J60.1, J60.4, J70.11, JP62.2, PS1.3, Q21.2, Q22.2, Q23.2, Q81.2, Q91.2, Q92.2, Q93.2, R21.1, R22.1, R23.1, R55.1, R56.1, R62.2, R81.2, R82.1, R91.2, R92.2, R93.2, R102.1, SW1.1, SW2.1, U1.1, U1.15, U1.38, U1.39, U2.3, U2.29, U61.5, U61.14, U101.5
HX_CLK: J70.4, U1.16, U61.11
HX_DATA: J70.8, U1.6, U61.12
IO0: Q51.3, R2.2, R53.2, U1.25
unnamed: C61.1, R63.2, U61.7
unnamed: C61.2, R64.2, U61.8
unnamed: C62.1, U61.6
unnamed: C63.1, C64.1, C65.1, JP61.1, Q61.1, R65.1, U61.1, U61.16
unnamed: C102.1, D101.1, L101.1, U101.1
unnamed: C102.2, U101.6
unnamed: D1.2, R3.2
unnamed: D80.1, R83.1
unnamed: D80.2, U81.3
unnamed: D81.2, R84.2
unnamed: D91.2, R94.2
unnamed: D92.2, R95.2
unnamed: D93.2, R96.2
unnamed: J21.2, Q21.3
unnamed: J21.3, Q22.3
unnamed: J21.4, Q23.3
unnamed: J51.A5, R55.2
unnamed: J51.B5, R56.2
unnamed: JP62.1, R65.2, U61.15
unnamed: K81.-, Q81.3
unnamed: K91.-, Q91.3
unnamed: K92.-, Q92.3
unnamed: K93.-, Q93.3
unnamed: Q51.2, R51.1
unnamed: Q52.2, R52.1
unnamed: Q61.2, U61.2
unnamed: R3.1, U1.14
unnamed: R61.2, R62.1, U61.4
unnamed: R83.2, U81.2
unnamed: R101.1, R102.2
unnamed: R101.2, R103.2, U101.4
RXD: U1.34, U2.25
SPI_CLK: J70.7, U1.30
SPI_CS0: J70.3, U1.29
SPI_MISO: J70.9, U1.31
SPI_MOSI: J70.1, U1.37
SPI_RES: J70.5, U1.33
TXD: R5.1, U2.26

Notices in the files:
parts and their libraries:
Copyright 2016 Accelerated Designs. All rights reserved.
